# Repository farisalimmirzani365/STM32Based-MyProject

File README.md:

# STM32Based-MyProject
The Board is based on the STM32 microcontroller, with the Blue Pill STM32F103 serving as the reference material for schematic design. This board is equipped with communication options, either the nRF24L01 or LoRa-02, which can be externally selected according to the user's preference. Additionally, the board features an integrated ADXL345 sensor. It includes a TF-Card for additional data storage. Furthermore, the board can be augmented with an external TFT LCD, which users can purchase separately.

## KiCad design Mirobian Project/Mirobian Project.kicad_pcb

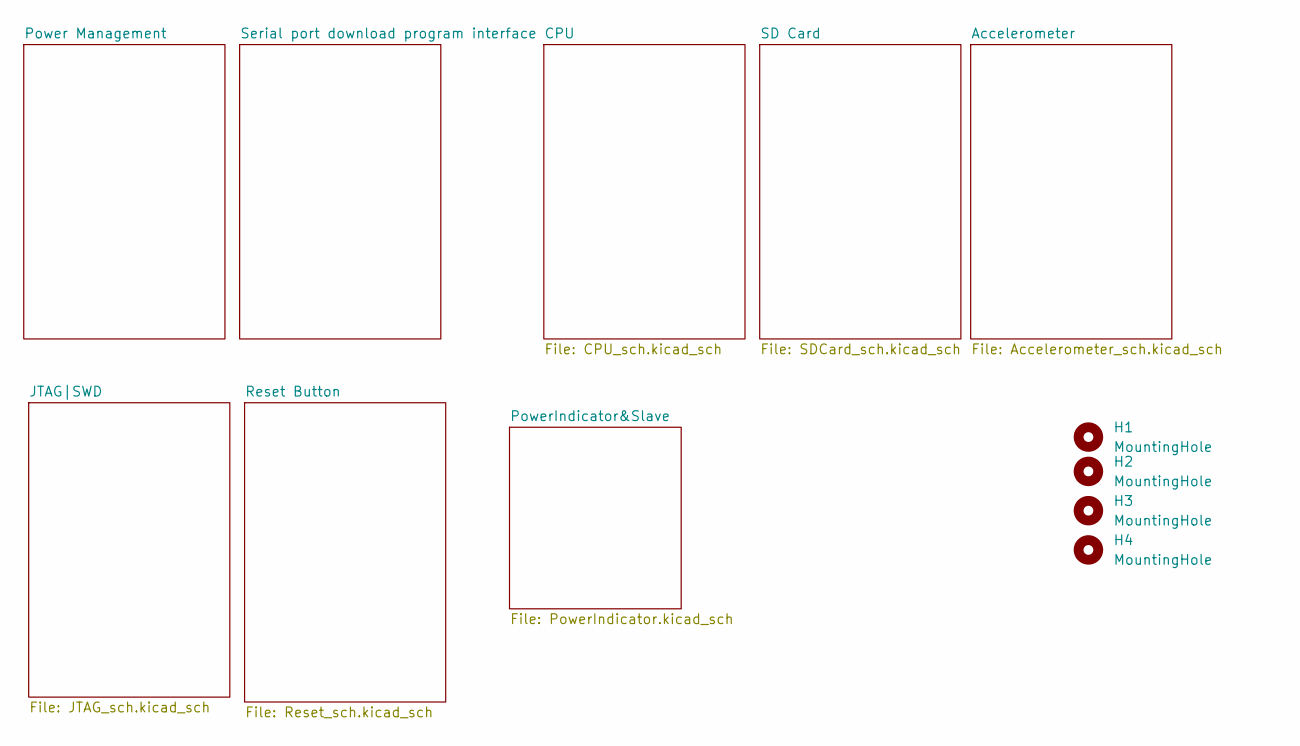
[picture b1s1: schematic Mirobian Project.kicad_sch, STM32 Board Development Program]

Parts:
H1, H2, H3, H4: MountingHole; MountingHole_2.2mm_M2

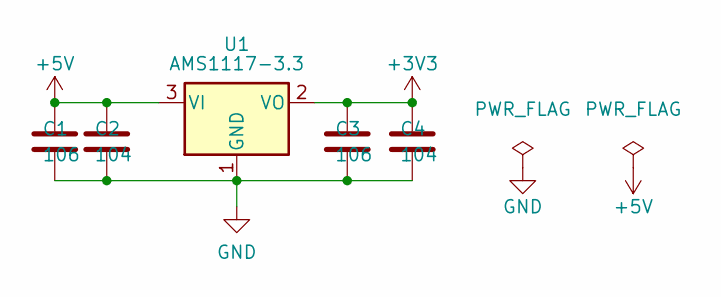
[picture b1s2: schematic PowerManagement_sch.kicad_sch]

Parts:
C1, C3: 106; C_0805_2012Metric_Pad1.18x1.45mm_HandSolder
C2, C4: 104; C_0603_1608Metric_Pad1.08x0.95mm_HandSolder
U1: AMS1117-3.3; SOT-223-3_TabPin2

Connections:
+5V: C1.1, C2.1, U1.3 (VI); also elsewhere on the board
DAT1: C3.1, C4.1, U1.2 (VO); also elsewhere on the board
VSS: C1.2, C2.2, C3.2, C4.2, U1.1 (GND); also elsewhere on the board

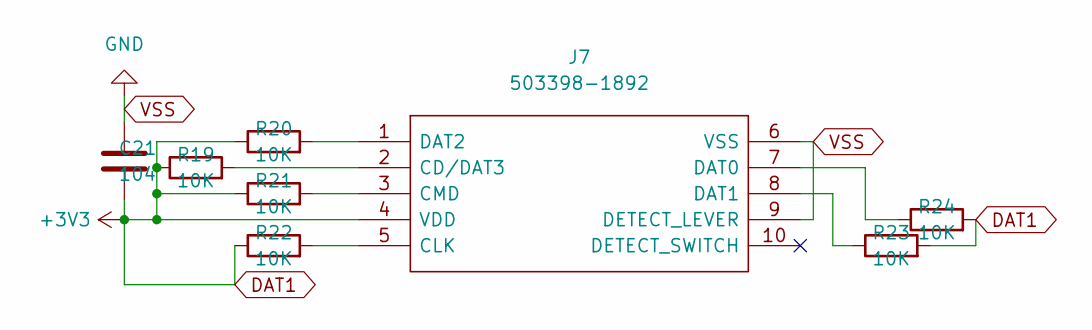
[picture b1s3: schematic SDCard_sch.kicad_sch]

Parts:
C21: 104; C_0603_1608Metric_Pad1.08x0.95mm_HandSolder
J7: 503398-1892; Manufacturer_Part_Number 503398-1892; Mouser Part Number 538-503398-1892
R19, R20, R21, R22, R23, R24: 10K; R_0201_0603Metric_Pad0.64x0.40mm_HandSolder

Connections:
DAT1: C21.2, J7.4 (VDD), R19.1, R20.1, R21.1, R22.1, R23.2, R24.2; also elsewhere on the board
unnamed: J7.1 (DAT2), R20.2
unnamed: J7.2 (CD/DAT3), R19.2
unnamed: J7.3 (CMD), R21.2
unnamed: J7.5 (CLK), R22.2
unnamed: J7.7 (DAT0), R24.1
unnamed: J7.8 (DAT1), R23.1
VSS: C21.1, J7.6 (VSS), J7.9 (DETECT_LEVER); also elsewhere on the board

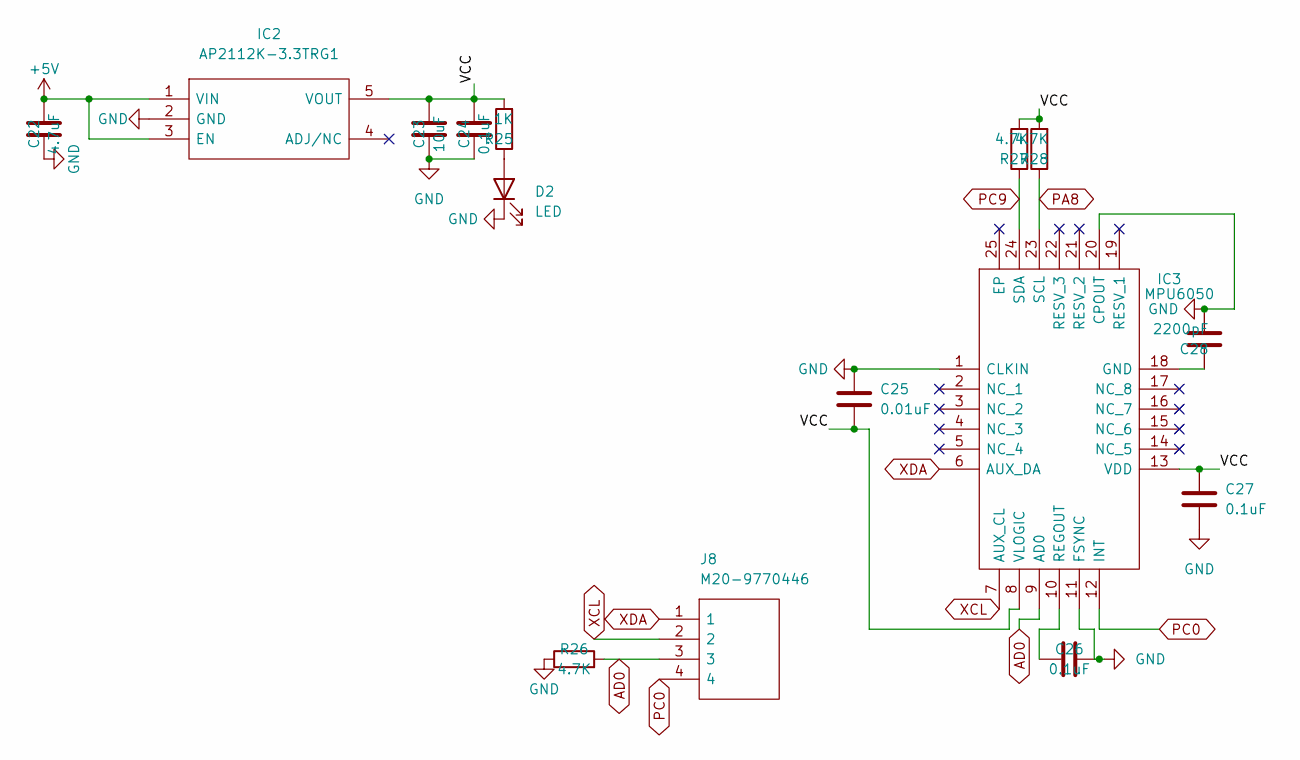
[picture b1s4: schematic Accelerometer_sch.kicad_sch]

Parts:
C22: 4.7uF; C_0603_1608Metric_Pad1.08x0.95mm_HandSolder
C23: 10uF; C_0603_1608Metric_Pad1.08x0.95mm_HandSolder
C24, C26, C27: 0.1uF; C_0603_1608Metric_Pad1.08x0.95mm_HandSolder
C25: 0.01uF; C_0805_2012Metric_Pad1.18x1.45mm_HandSolder
C28: 2200pF; C_0805_2012Metric_Pad1.18x1.45mm_HandSolder
D2: LED; LED_0805_2012Metric_Pad1.15x1.40mm_HandSolder
IC2: AP2112K-3.3TRG1; SOT95P282X130-5N; Manufacturer_Part_Number AP2112K-3.3TRG1; Mouser Part Number 621-AP2112K-3.3TRG1
IC3: MPU6050; Manufacturer_Part_Number MPU6050
J8: M20-9770446; HDRV4W64P0X254_1X4_1016X254X834P; Manufacturer_Part_Number M20-9770446; Mouser Part Number 855-M20-9770446
R25: 1K; R_0201_0603Metric_Pad0.64x0.40mm_HandSolder
R26, R27, R28: 4.7K; C_0603_1608Metric_Pad1.08x0.95mm_HandSolder

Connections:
+5V: C22.2, IC2.1 (VIN), IC2.3 (EN); also elsewhere on the board
/Accelerometer/VCC: C23.2, C24.2, C25.2, C27.1, IC2.5 (VOUT), IC3.8 (VLOGIC), IC3.13 (VDD), R25.2, R27.2, R28.2
AD0: IC3.9 (AD0), J8.3, R26.2
unnamed: C26.1, IC3.10 (REGOUT)
unnamed: C28.1, IC3.18 (GND)
unnamed: D2.2 (A), R25.1
PA8: IC3.23 (SCL), R28.1; also elsewhere on the board
PC0: IC3.12 (INT), J8.4; also elsewhere on the board
PC9: IC3.24 (SDA), R27.1; also elsewhere on the board
VSS: C22.1, C23.1, C24.1, C25.1, C26.2, C27.2, C28.2, D2.1 (K), IC2.2 (GND), IC3.1 (CLKIN), IC3.11 (FSYNC), IC3.20 (CPOUT), R26.1; also elsewhere on the board
XCL: IC3.7 (AUX_CL), J8.2
XDA: IC3.6 (AUX_DA), J8.1

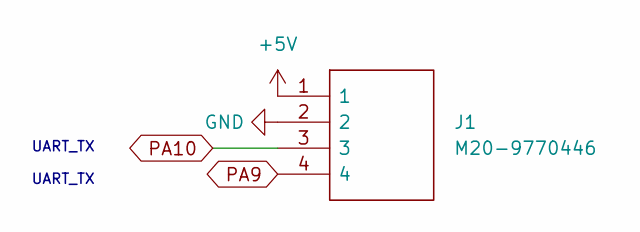
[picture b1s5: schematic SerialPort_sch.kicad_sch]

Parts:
J1: M20-9770446; HDRV4W64P0X254_1X4_1016X254X834P; Manufacturer_Part_Number M20-9770446; Mouser Part Number 855-M20-9770446

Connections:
+5V: J1.1; also elsewhere on the board
PA9: J1.4; also elsewhere on the board
PA10: J1.3; also elsewhere on the board
VSS: J1.2; also elsewhere on the board

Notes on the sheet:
UART_TX

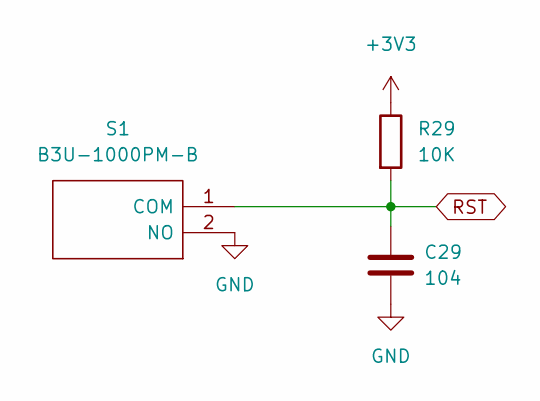
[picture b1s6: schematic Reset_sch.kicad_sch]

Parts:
C29: 104; C_0603_1608Metric_Pad1.08x0.95mm_HandSolder
R29: 10K; R_0603_1608Metric_Pad0.98x0.95mm_HandSolder
S1: B3U-1000PM-B; B3U1000PMB; Manufacturer_Part_Number B3U-1000PM-B; Mouser Part Number 653-B3U-1000PM-B

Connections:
DAT1: R29.1; also elsewhere on the board
RST: C29.1, R29.2, S1.1 (COM); also elsewhere on the board
VSS: C29.2, S1.2 (NO); also elsewhere on the board

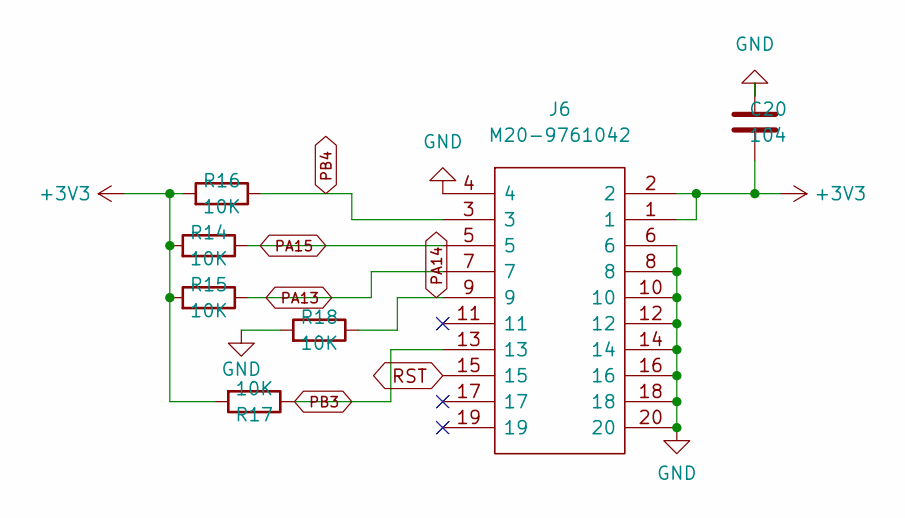
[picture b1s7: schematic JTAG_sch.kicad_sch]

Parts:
C20: 104; C_0201_0603Metric_Pad0.64x0.40mm_HandSolder
J6: M20-9761042; HDRV20W64P254_2X10_2540X508X838P; Manufacturer_Part_Number M20-9761042; Mouser Part Number 855-M20-9761042
R14, R15, R16, R17, R18: 10K; R_0201_0603Metric_Pad0.64x0.40mm_HandSolder

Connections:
DAT1: C20.2, J6.1, J6.2, R14.2, R15.2, R16.2, R17.2; also elsewhere on the board
PA13: J6.7, R15.1; also elsewhere on the board
PA14: J6.9, R18.1; also elsewhere on the board
PA15: J6.5, R14.1; also elsewhere on the board
PB3: J6.13, R17.1; also elsewhere on the board
PB4: J6.3, R16.1; also elsewhere on the board
RST: J6.15; also elsewhere on the board
VSS: C20.1, J6.4, J6.6, J6.8, J6.10, J6.12, J6.14, J6.16, J6.18, J6.20, R18.2; also elsewhere on the board

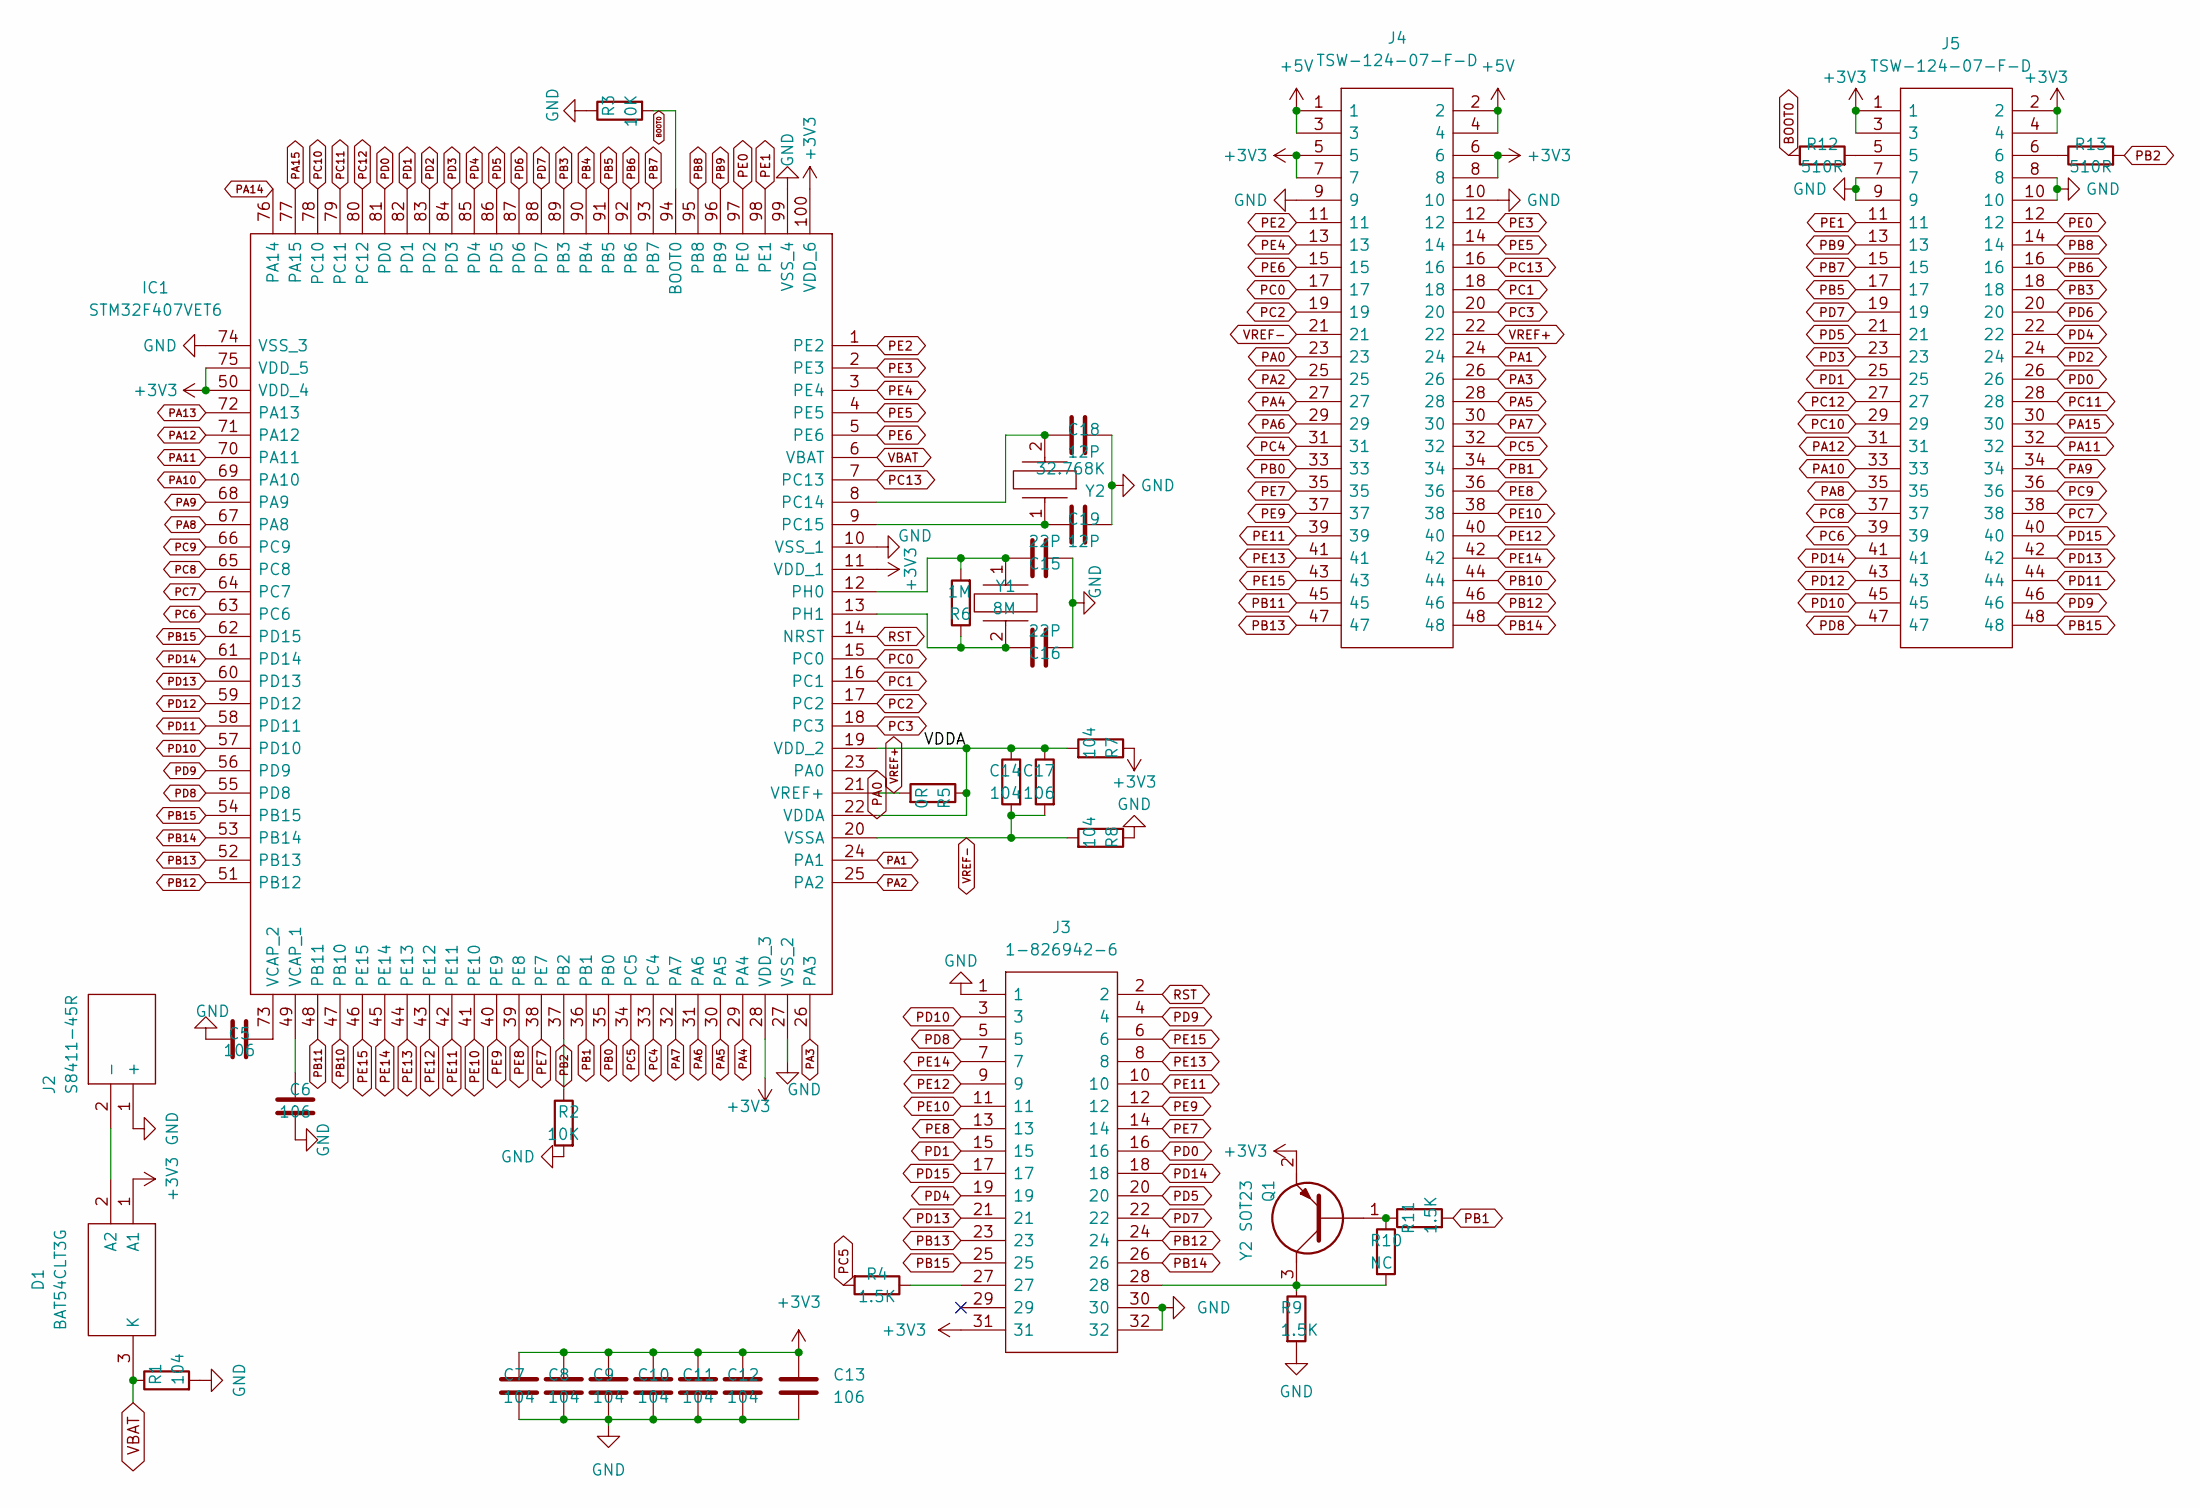
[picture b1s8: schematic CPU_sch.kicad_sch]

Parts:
C5, C6, C13, C17: 106; C_0805_2012Metric_Pad1.18x1.45mm_HandSolder
C7, C8, C9, C10, C11, C12, C14: 104; C_0603_1608Metric_Pad1.08x0.95mm_HandSolder
C15, C16: 22P; C_0805_2012Metric_Pad1.18x1.45mm_HandSolder
C18, C19: 12P; C_0805_2012Metric_Pad1.18x1.45mm_HandSolder
D1: BAT54CLT3G; SOT96P237X111-3N; Manufacturer_Part_Number BAT54CLT3G; Mouser Part Number 863-BAT54CLT3G
IC1: STM32F407VET6; QFP50P1600X1600X160-100N; Manufacturer_Part_Number STM32F407VET6; Mouser Part Number 511-STM32F407VET6
J2: S8411-45R; S8411-45R_1; Manufacturer_Part_Number S8411-45R; Mouser Part Number 855-S8411-45R
J3: 1-826942-6; HDRV32W63P254_2X16_4114X500X860P; Manufacturer_Part_Number 1-826942-6; Mouser Part Number 571-1-826942-6
J4, J5: TSW-124-07-F-D; TSW-124-XX-YY-D; Manufacturer_Part_Number TSW-124-07-F-D; Mouser Part Number 200-TSW12407FD
Q1: Y2 SOT23; SOT96P240X110-3N; Manufacturer_Part_Number MMBT3906-7-F; Mouser Part Number 621-MMBT3906-F
R1, R7, R8: 104; R_0603_1608Metric_Pad0.98x0.95mm_HandSolder
R2: 10K; C_0603_1608Metric_Pad1.08x0.95mm_HandSolder
R3: 10K; R_0201_0603Metric_Pad0.64x0.40mm_HandSolder
R4, R9, R11: 1.5K; R_0603_1608Metric_Pad0.98x0.95mm_HandSolder
R5: 0R; R_0603_1608Metric_Pad0.98x0.95mm_HandSolder
R6: 1M; R_0603_1608Metric_Pad0.98x0.95mm_HandSolder
R10: NC; R_0603_1608Metric_Pad0.98x0.95mm_HandSolder
R12, R13: 510R; R_0603_1608Metric_Pad0.98x0.95mm_HandSolder
Y1: 8M; LFXTAL057135Bulk; Manufacturer_Part_Number LFXTAL057135Bulk; Mouser Part Number 449-LFXTAL057135BULK
Y2: 32.768K; LFXTAL057135Bulk; Manufacturer_Part_Number LFXTAL057135Bulk; Mouser Part Number 449-LFXTAL057135BULK

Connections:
+5V: J4.1, J4.2, J4.3, J4.4; also elsewhere on the board
/CPU/VDDA: C14.1, C17.1, IC1.19 (VDD_2), IC1.22 (VDDA), R5.1, R7.2
BOOT0: IC1.94 (BOOT0), R3.2, R12.1
DAT1: C7.1, C8.1, C9.1, C10.1, C11.1, C12.1, C13.1, D1.1 (A1), IC1.11 (VDD_1), IC1.28 (VDD_3), IC1.50 (VDD_4), IC1.75 (VDD_5), IC1.100 (VDD_6), J3.31, J4.5, J4.6, J4.7, J4.8, J5.1, J5.2, J5.3, J5.4, Q1.2, R7.1; also elsewhere on the board
unnamed: C5.2, IC1.73 (VCAP_2)
unnamed: C6.1, IC1.49 (VCAP_1)
unnamed: C15.2, IC1.12 (PH0), R6.2, Y1.1
unnamed: C16.2, IC1.13 (PH1), R6.1, Y1.2
unnamed: C18.2, IC1.8 (PC14), Y2.2
unnamed: C19.2, IC1.9 (PC15), Y2.1
unnamed: D1.2 (A2), J2.2 (-)
unnamed: J3.27, R4.1
unnamed: J3.28, Q1.3, R9.1, R10.2
unnamed: J5.5, R12.2
unnamed: J5.6, R13.1
unnamed: Q1.1, R10.1, R11.1
PA0: IC1.23 (PA0), J4.23; also elsewhere on the board
PA1: IC1.24 (PA1), J4.24; also elsewhere on the board
PA2: IC1.25 (PA2), J4.25
PA3: IC1.26 (PA3), J4.26
PA4: IC1.29 (PA4), J4.27; also elsewhere on the board
PA5: IC1.30 (PA5), J4.28; also elsewhere on the board
PA6: IC1.31 (PA6), J4.29; also elsewhere on the board
PA7: IC1.32 (PA7), J4.30; also elsewhere on the board
PA8: IC1.67 (PA8), J5.35; also elsewhere on the board
PA9: IC1.68 (PA9), J5.34; also elsewhere on the board
PA10: IC1.69 (PA10), J5.33; also elsewhere on the board
PA11: IC1.70 (PA11), J5.32; also elsewhere on the board
PA12: IC1.71 (PA12), J5.31; also elsewhere on the board
PA13: IC1.72 (PA13); also elsewhere on the board
PA14: IC1.76 (PA14); also elsewhere on the board
PA15: IC1.77 (PA15), J5.30; also elsewhere on the board
PB0: IC1.35 (PB0), J4.33; also elsewhere on the board
PB1: IC1.36 (PB1), J4.34, R11.2
PB2: IC1.37 (PB2), R2.1, R13.2
PB3: IC1.89 (PB3), J5.18; also elsewhere on the board
PB4: IC1.90 (PB4); also elsewhere on the board
PB5: IC1.91 (PB5), J5.17; also elsewhere on the board
PB6: IC1.92 (PB6), J5.16; also elsewhere on the board
PB7: IC1.93 (PB7), J5.15; also elsewhere on the board
PB8: IC1.95 (PB8), J5.14; also elsewhere on the board
PB9: IC1.96 (PB9), J5.13
PB10: IC1.47 (PB10), J4.44
PB11: IC1.48 (PB11), J4.45
PB12: IC1.51 (PB12), J3.24, J4.46
PB13: IC1.52 (PB13), J3.23, J4.47
PB14: IC1.53 (PB14), J3.26, J4.48
PB15: IC1.54 (PB15), IC1.62 (PD15), J3.25, J5.48
PC0: IC1.15 (PC0), J4.17; also elsewhere on the board
PC1: IC1.16 (PC1), J4.18
PC2: IC1.17 (PC2), J4.19
PC3: IC1.18 (PC3), J4.20
PC4: IC1.33 (PC4), J4.31
PC5: IC1.34 (PC5), J4.32, R4.2
PC6: IC1.63 (PC6), J5.39
PC7: IC1.64 (PC7), J5.38
PC8: IC1.65 (PC8), J5.37
PC9: IC1.66 (PC9), J5.36; also elsewhere on the board
PC10: IC1.78 (PC10), J5.29
PC11: IC1.79 (PC11), J5.28
PC12: IC1.80 (PC12), J5.27
PC13: IC1.7 (PC13), J4.16
PD0: IC1.81 (PD0), J3.16, J5.26
PD1: IC1.82 (PD1), J3.15, J5.25
PD2: IC1.83 (PD2), J5.24
PD3: IC1.84 (PD3), J5.23
PD4: IC1.85 (PD4), J3.19, J5.22
PD5: IC1.86 (PD5), J3.20, J5.21
PD6: IC1.87 (PD6), J5.20
PD7: IC1.88 (PD7), J3.22, J5.19
PD8: IC1.55 (PD8), J3.5, J5.47
PD9: IC1.56 (PD9), J3.4, J5.46
PD10: IC1.57 (PD10), J3.3, J5.45
PD11: IC1.58 (PD11), J5.44
PD12: IC1.59 (PD12), J5.43
PD13: IC1.60 (PD13), J3.21, J5.42
PD14: IC1.61 (PD14), J3.18, J5.41
PD15: J3.17, J5.40
PE0: IC1.97 (PE0), J5.12
PE1: IC1.98 (PE1), J5.11
PE2: IC1.1 (PE2), J4.11
PE3: IC1.2 (PE3), J4.12; also elsewhere on the board
PE4: IC1.3 (PE4), J4.13; also elsewhere on the board
PE5: IC1.4 (PE5), J4.14
PE6: IC1.5 (PE6), J4.15
PE7: IC1.38 (PE7), J3.14, J4.35
PE8: IC1.39 (PE8), J3.13, J4.36
PE9: IC1.40 (PE9), J3.12, J4.37
PE10: IC1.41 (PE10), J3.11, J4.38
PE11: IC1.42 (PE11), J3.10, J4.39
PE12: IC1.43 (PE12), J3.9, J4.40
PE13: IC1.44 (PE13), J3.8, J4.41
PE14: IC1.45 (PE14), J3.7, J4.42
PE15: IC1.46 (PE15), J3.6, J4.43
RST: IC1.14 (NRST), J3.2; also elsewhere on the board
VBAT: D1.3 (K), IC1.6 (VBAT), R1.1
VREF+: IC1.21 (VREF+), J4.22, R5.2
VREF-: C14.2, C17.2, IC1.20 (VSSA), J4.21, R8.2
VSS: C5.1, C6.2, C7.2, C8.2, C9.2, C10.2, C11.2, C12.2, C13.2, C15.1, C16.1, C18.1, C19.1, IC1.10 (VSS_1), IC1.27 (VSS_2), IC1.74 (VSS_3), IC1.99 (VSS_4), J2.1 (+), J3.1, J3.30, J3.32, J4.9, J4.10, J5.7, J5.8, J5.9, J5.10, R1.2, R2.2, R3.1, R8.1, R9.2; also elsewhere on the board

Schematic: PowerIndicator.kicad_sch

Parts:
D3, D4, D5: LED; LED_0805_2012Metric_Pad1.15x1.40mm_HandSolder
IC4: W25Q16JVZPIQ; SON127P600X500X80-9N-D; Manufacturer_Part_Number W25Q16JVZPIQ; Mouser Part Number 454-W25Q16JVZPIQ
J9: G800LS588010THR; HDRV16W64P254_2X8_2032X500X885P; Manufacturer_Part_Number G800LS588010THR; Mouser Part Number 523-G800LS588010THR
J10: 105164-0001; 1051640001; Manufacturer_Part_Number 105164-0001; Mouser Part Number 538-105164-0001
R30, R32, R33: 510; LED_0603_1608Metric_Pad1.05x0.95mm_HandSolder
R31, R35: 10K; LED_0603_1608Metric_Pad1.05x0.95mm_HandSolder
R34, R37: 22; LED_0603_1608Metric_Pad1.05x0.95mm_HandSolder
R36: 1.5K; LED_0603_1608Metric_Pad1.05x0.95mm_HandSolder
R38: 500mA; LED_0805_2012Metric_Pad1.15x1.40mm_HandSolder
R39, R40: 22R; LED_0603_1608Metric_Pad1.05x0.95mm_HandSolder
S2, S3, S4: B3U-1000PM-B; B3U1000PMB; Manufacturer_Part_Number B3U-1000PM-B; Mouser Part Number 653-B3U-1000PM-B

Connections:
+5V: R38.1; also elsewhere on the board
DAT1: D4.1 (K), D5.1 (K), IC4.3 (IO2), IC4.7 (IO3), IC4.8 (VCC), J9.2, R30.1, R31.1, R35.1, R36.1, R39.1; also elsewhere on the board
unnamed: D3.2 (A), R30.2
unnamed: D4.2 (A), R32.2
unnamed: D5.2 (A), R33.2
unnamed: IC4.6 (CLK), R40.1
unnamed: J10.2 (D-), R37.2
unnamed: J10.3 (D+), R34.2, R36.2
unnamed: R31.2, S4.2 (NO)
PA0: S4.1 (COM); also elsewhere on the board
PA1: J9.16; also elsewhere on the board
PA4: J9.15; also elsewhere on the board
PA5: J9.12; also elsewhere on the board
PA6: J9.13, R33.1; also elsewhere on the board
PA7: J9.14, R32.1; also elsewhere on the board
PA11: R37.1; also elsewhere on the board
PA12: R34.1; also elsewhere on the board
PB0: IC4.1 (~CS), J9.11, R35.2; also elsewhere on the board
PB3: J9.5, R40.2; also elsewhere on the board
PB4: IC4.2 (DO_(IO1)), J9.7; also elsewhere on the board
PB5: IC4.5 (DI_(IO0)), J9.6; also elsewhere on the board
PB6: J9.3; also elsewhere on the board
PB7: J9.4; also elsewhere on the board
PB8: J9.8; also elsewhere on the board
PE3: S2.2 (NO); also elsewhere on the board
PE4: S3.2 (NO); also elsewhere on the board
VBUS: J9.9, J10.1 (VBUS), R38.2
VSS: D3.1 (K), IC4.4 (GND), J9.1, J9.10, J10.5 (GND), R39.2, S2.1 (COM), S3.1 (COM); also elsewhere on the board

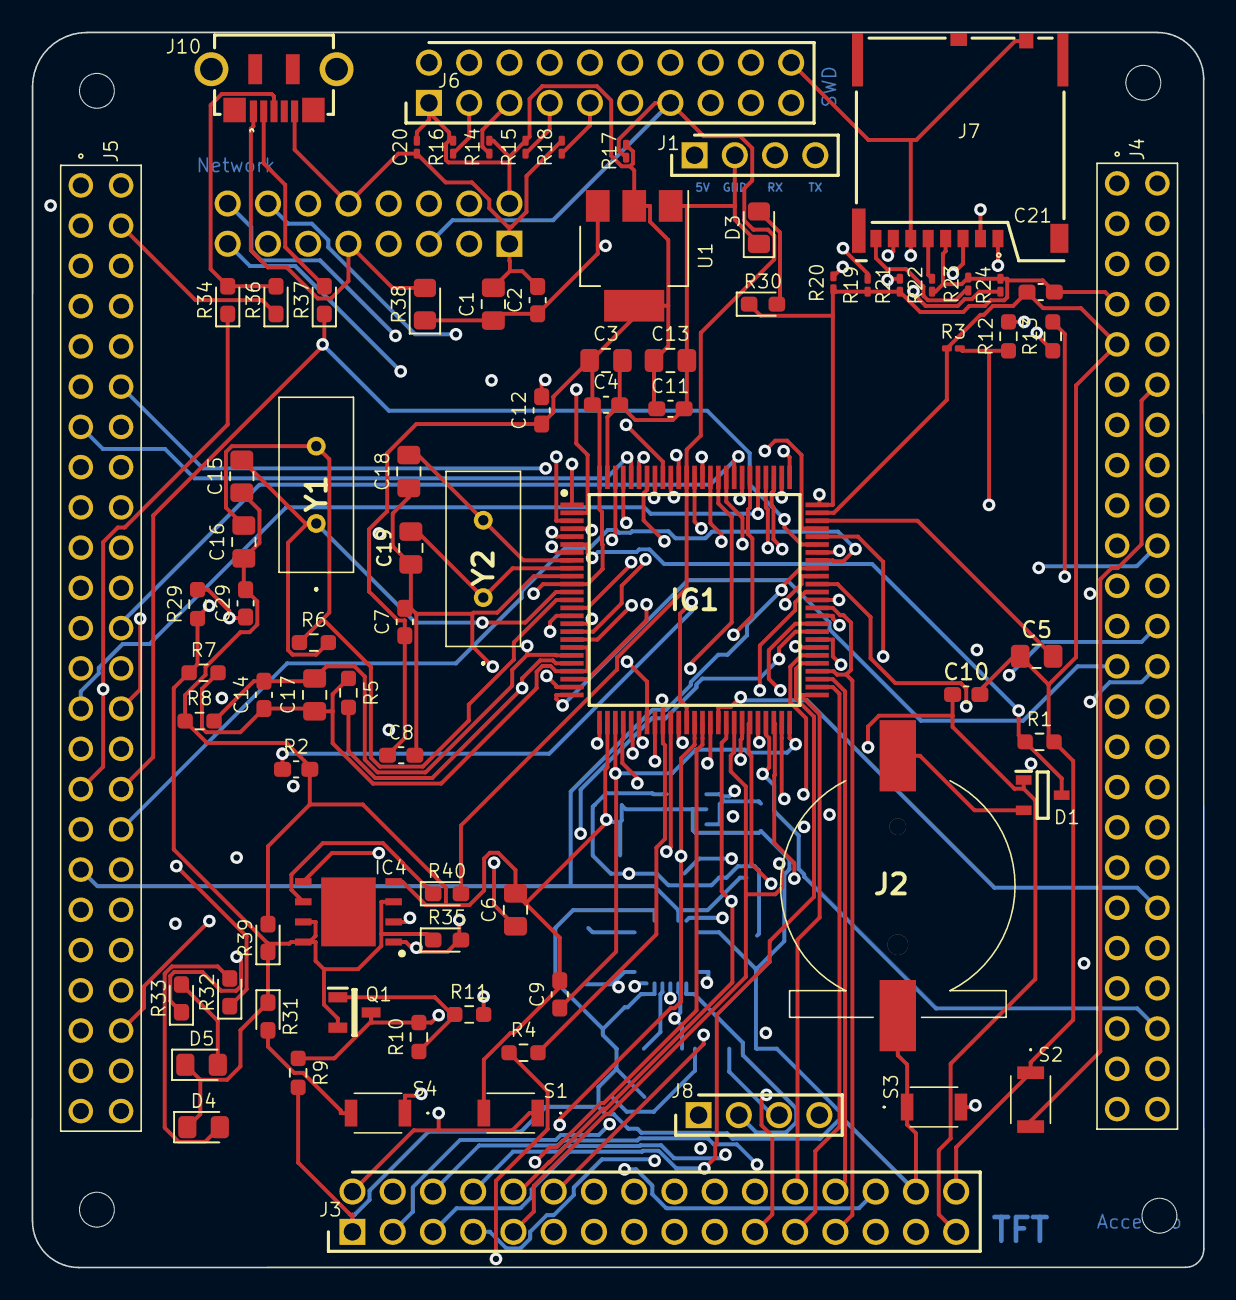
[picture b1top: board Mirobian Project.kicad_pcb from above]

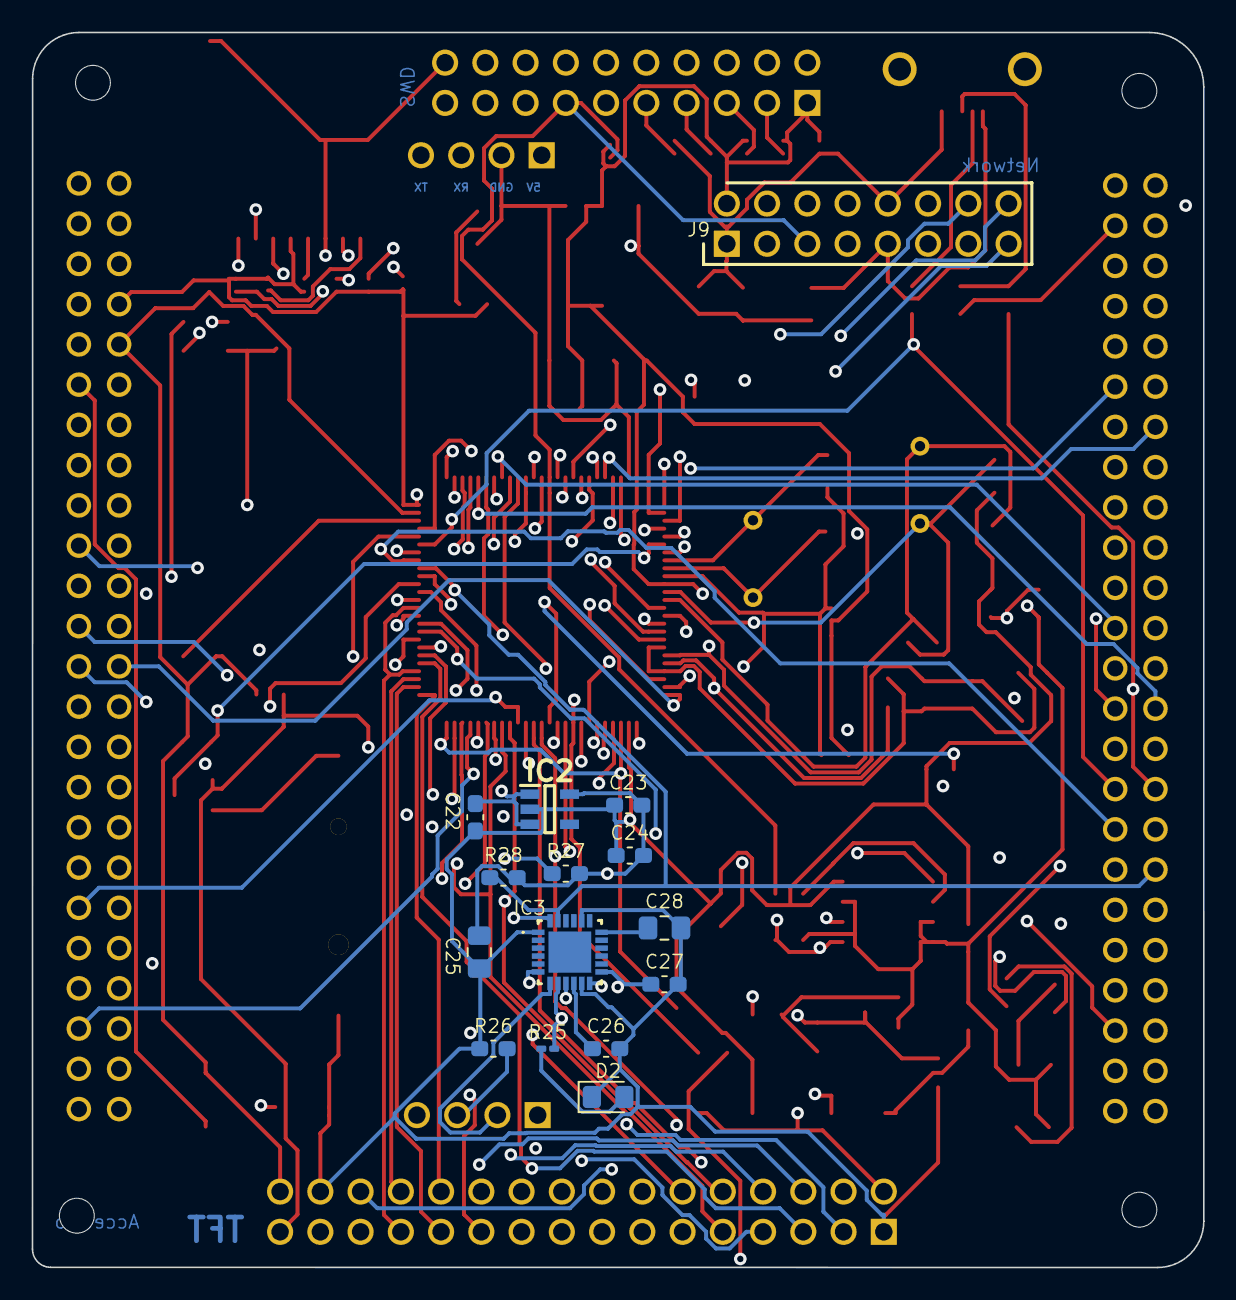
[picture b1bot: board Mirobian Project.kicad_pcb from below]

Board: 4 copper layers, 73.9 x 77.9 mm, 100 parts (15 on the bottom side), 120 nets.

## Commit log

2023-09-17 Add files via upload
    The Board is based on the STM32 microcontroller, with the Blue Pill STM32F103 serving as the reference material for schematic design. This board is equipped with communication options, either the nRF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
